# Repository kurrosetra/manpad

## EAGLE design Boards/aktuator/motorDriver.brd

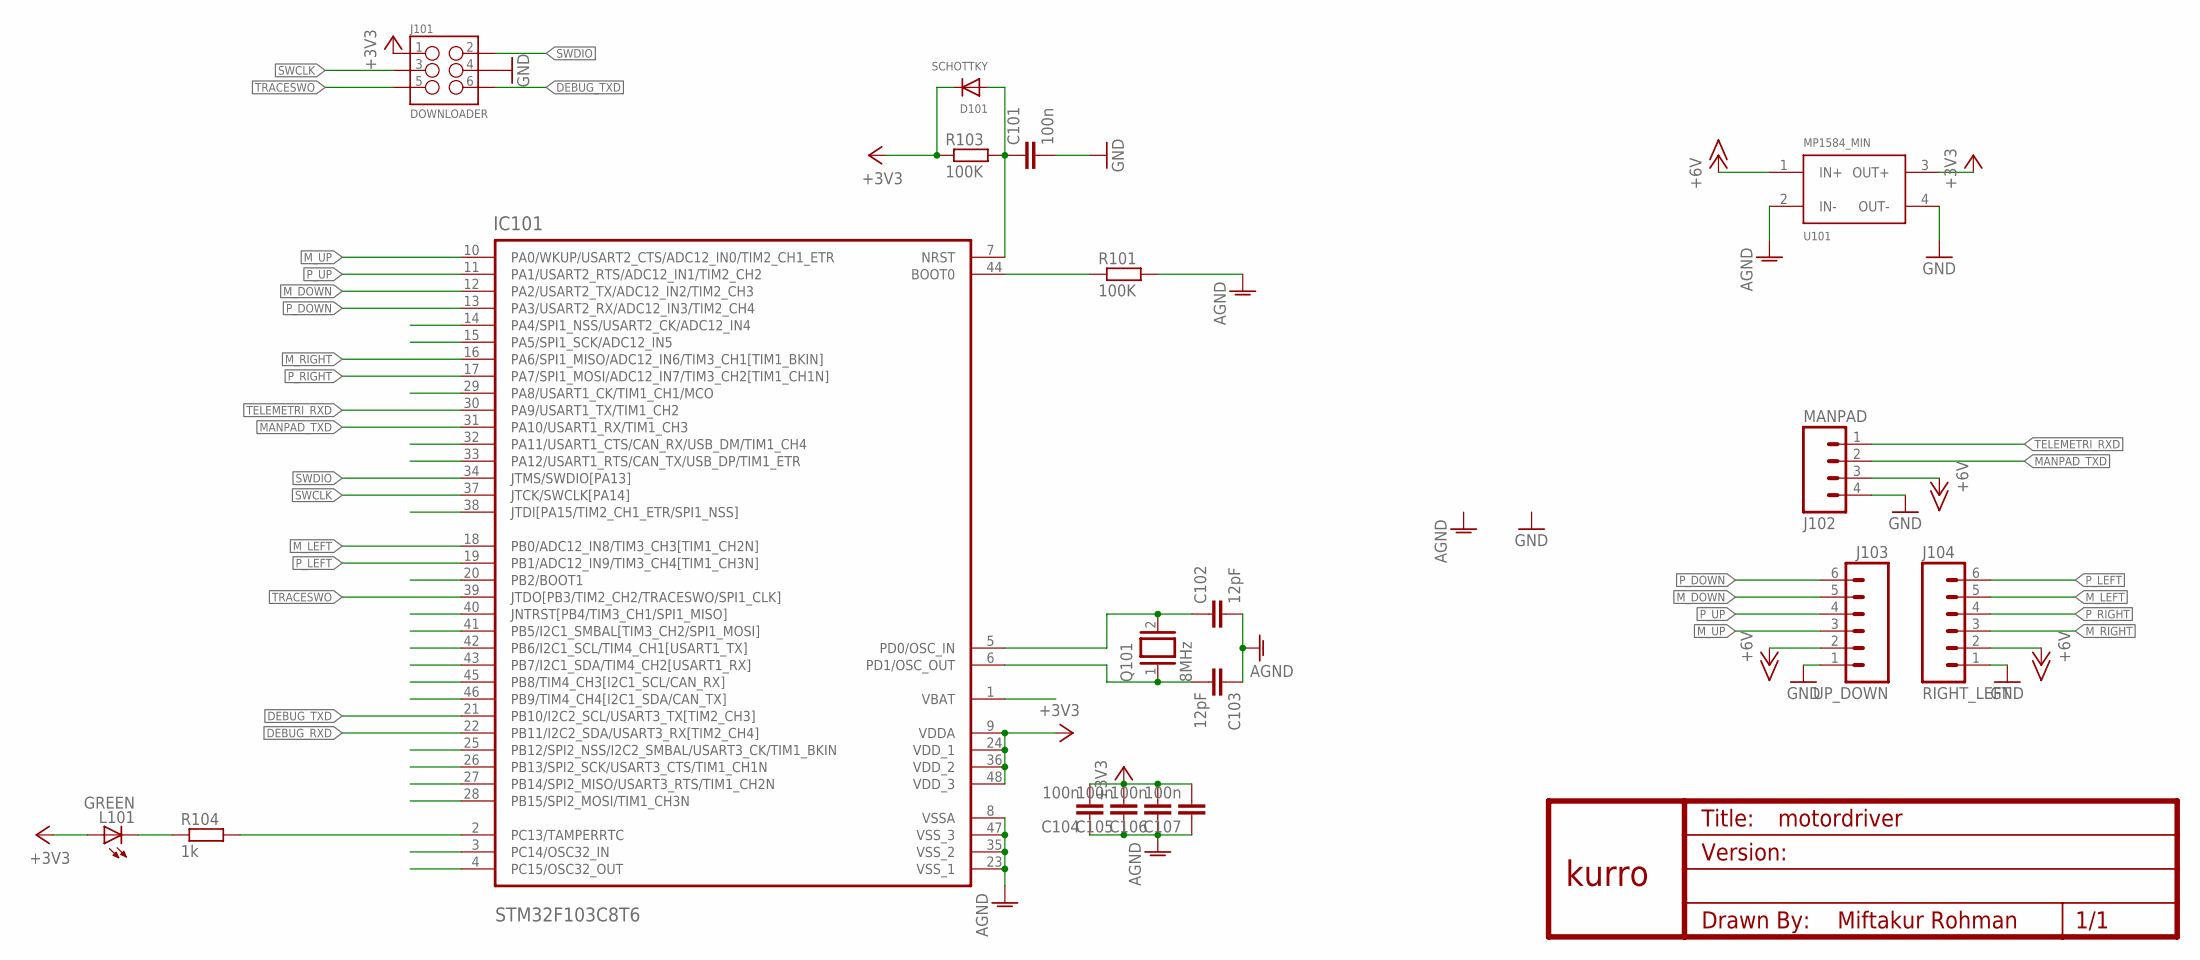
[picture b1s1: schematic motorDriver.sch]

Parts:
C101, C104, C105, C106, C107: 100n; C0603
C102, C103: 12pF; C0603
D101: SCHOTTKY; SOD-323F
IC101: STM32F103C8T6; QFP50P900X900X160-48N
J101: DOWNLOADER; 2X3_SMD
J102: MANPAD; XH-4-VERT-SMD
J103: UP_DOWN; XH-6-VERT-SMD
J104: RIGHT_LEFT; XH-6-VERT-SMD
L101: GREEN; CHIP-LED0805
Q101: 8MHz; QS
R101, R103: 100K; R0603
R104: 1k; R0603
U101: MP1584_MIN
U$1: KURRO_FOOTPRINT; KURRO-LOGO

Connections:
+3V3: C104.2, C105.2, C106.2, C107.2, D101.C, IC101.9 (VDDA), IC101.24 (VDD_1), IC101.36 (VDD_2), IC101.48 (VDD_3), J101.1, L101.A, R103.1, U101.3 (OUT+)
+6V: J102.3, J103.2, J104.2, U101.1 (IN+)
AGND: C102.2, C103.1, C104.1, C105.1, C106.1, C107.1, IC101.8 (VSSA), IC101.23 (VSS_1), IC101.35 (VSS_2), IC101.47 (VSS_3), R101.2, U101.2 (IN-)
DEBUG_RXD: IC101.22 (PB11/I2C2_SDA/USART3_RX[TIM2_CH4])
DEBUG_TXD: IC101.21 (PB10/I2C2_SCL/USART3_TX[TIM2_CH3]), J101.6
GND: C101.2, J101.4, J102.4, J103.1, J104.1, U101.4 (OUT-)
IMU1_SCL: IC101.42 (PB6/I2C1_SCL/TIM4_CH1[USART1_TX])
IMU1_SDA: IC101.43 (PB7/I2C1_SDA/TIM4_CH2[USART1_RX])
LED1_BUILTIN: IC101.2 (PC13/TAMPERRTC), R104.2
MANPAD_TXD: IC101.31 (PA10/USART1_RX/TIM1_CH3), J102.2
M_DOWN: IC101.12 (PA2/USART2_TX/ADC12_IN2/TIM2_CH3), J103.5
M_LEFT: IC101.18 (PB0/ADC12_IN8/TIM3_CH3[TIM1_CH2N]), J104.5
M_RIGHT: IC101.16 (PA6/SPI1_MISO/ADC12_IN6/TIM3_CH1[TIM1_B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), J104.3
M_UP: IC101.10 (PA0/WKUP/USART2_CTS/ADC12_IN0/TIM2_CH1_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), J103.3
unnamed: IC101.44 (BOOT0), R101.1
unnamed: C103.2, IC101.6 (PD1/OSC_OUT), Q101.1
unnamed: C102.1, IC101.5 (PD0/OSC_IN), Q101.2
unnamed: L101.C, R104.1
P_DOWN: IC101.13 (PA3/USART2_RX/ADC12_IN3/TIM2_CH4), J103.6
P_LEFT: IC101.19 (PB1/ADC12_IN9/TIM3_CH4[TIM1_CH3N]), J104.6
P_RIGHT: IC101.17 (PA7/SPI1_MOSI/ADC12_IN7/TIM3_CH2[TIM1_C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), J104.4
P_UP: IC101.11 (PA1/USART2_RTS/ADC12_IN1/TIM2_CH2), J103.4
RST: C101.1, D101.A, IC101.7 (NRST), R103.2
SWCLK: IC101.37 (JTCK/SWCLK[PA14]), J101.3
SWDIO: IC101.34 (JTMS/SWDIO[PA13]), J101.2
TELEMETRI_RXD: IC101.30 (PA9/USART1_TX/TIM1_CH2), J102.1
TRACESWO: IC101.39 (JTDO[PB3/TIM2_CH2/TRACESWO/SPI1_CLK]), J101.5

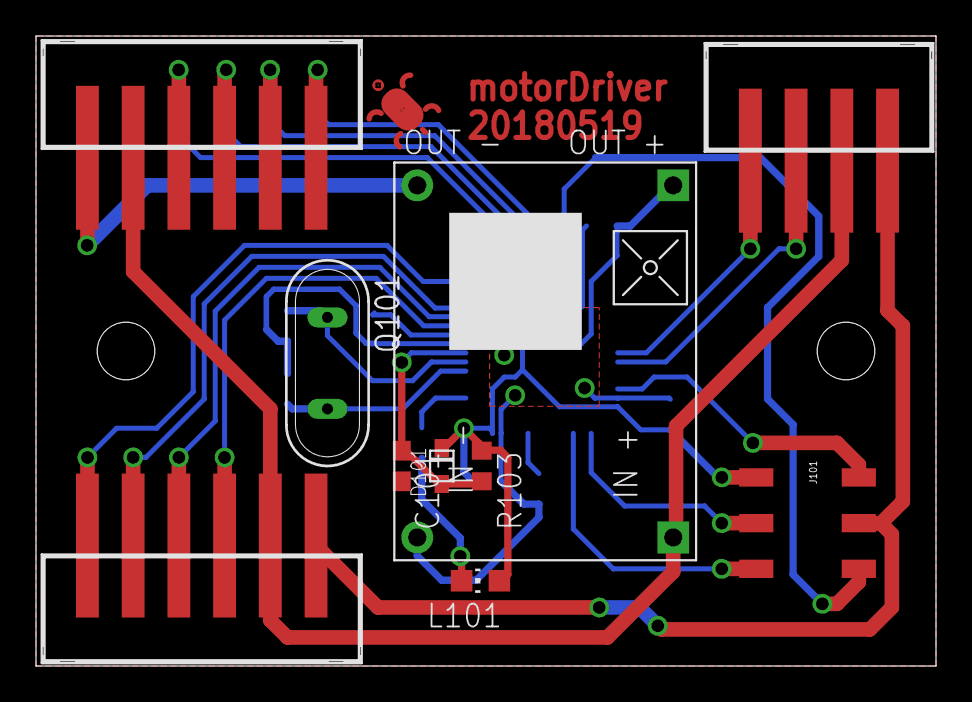
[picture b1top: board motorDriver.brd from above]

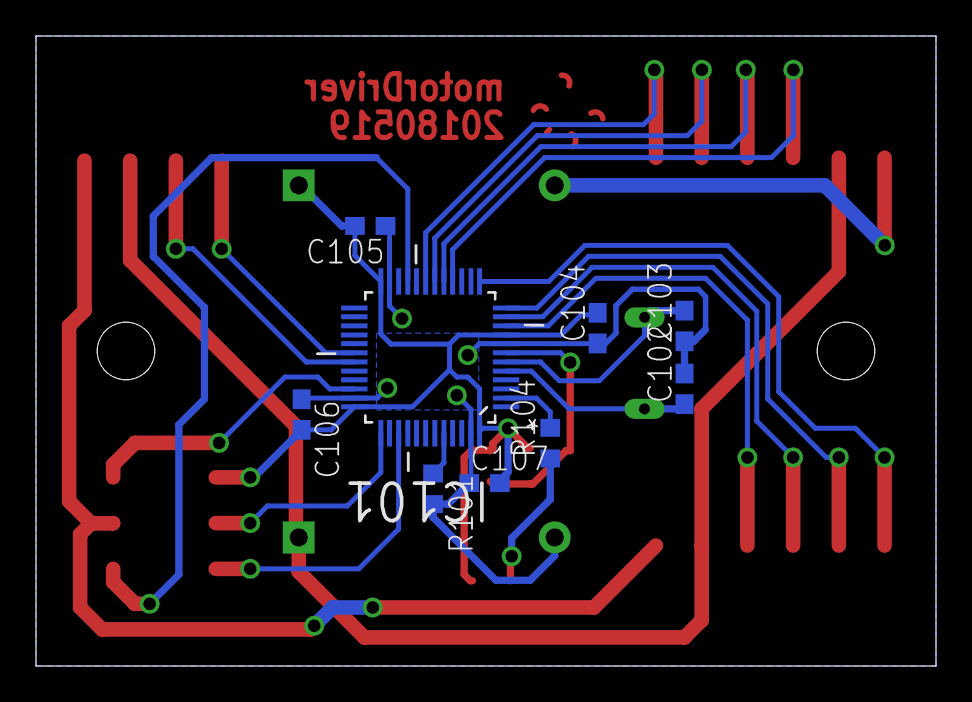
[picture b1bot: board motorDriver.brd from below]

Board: 2 copper layers, 50.0 x 35.0 mm, 20 parts (10 on the bottom side), 24 nets.

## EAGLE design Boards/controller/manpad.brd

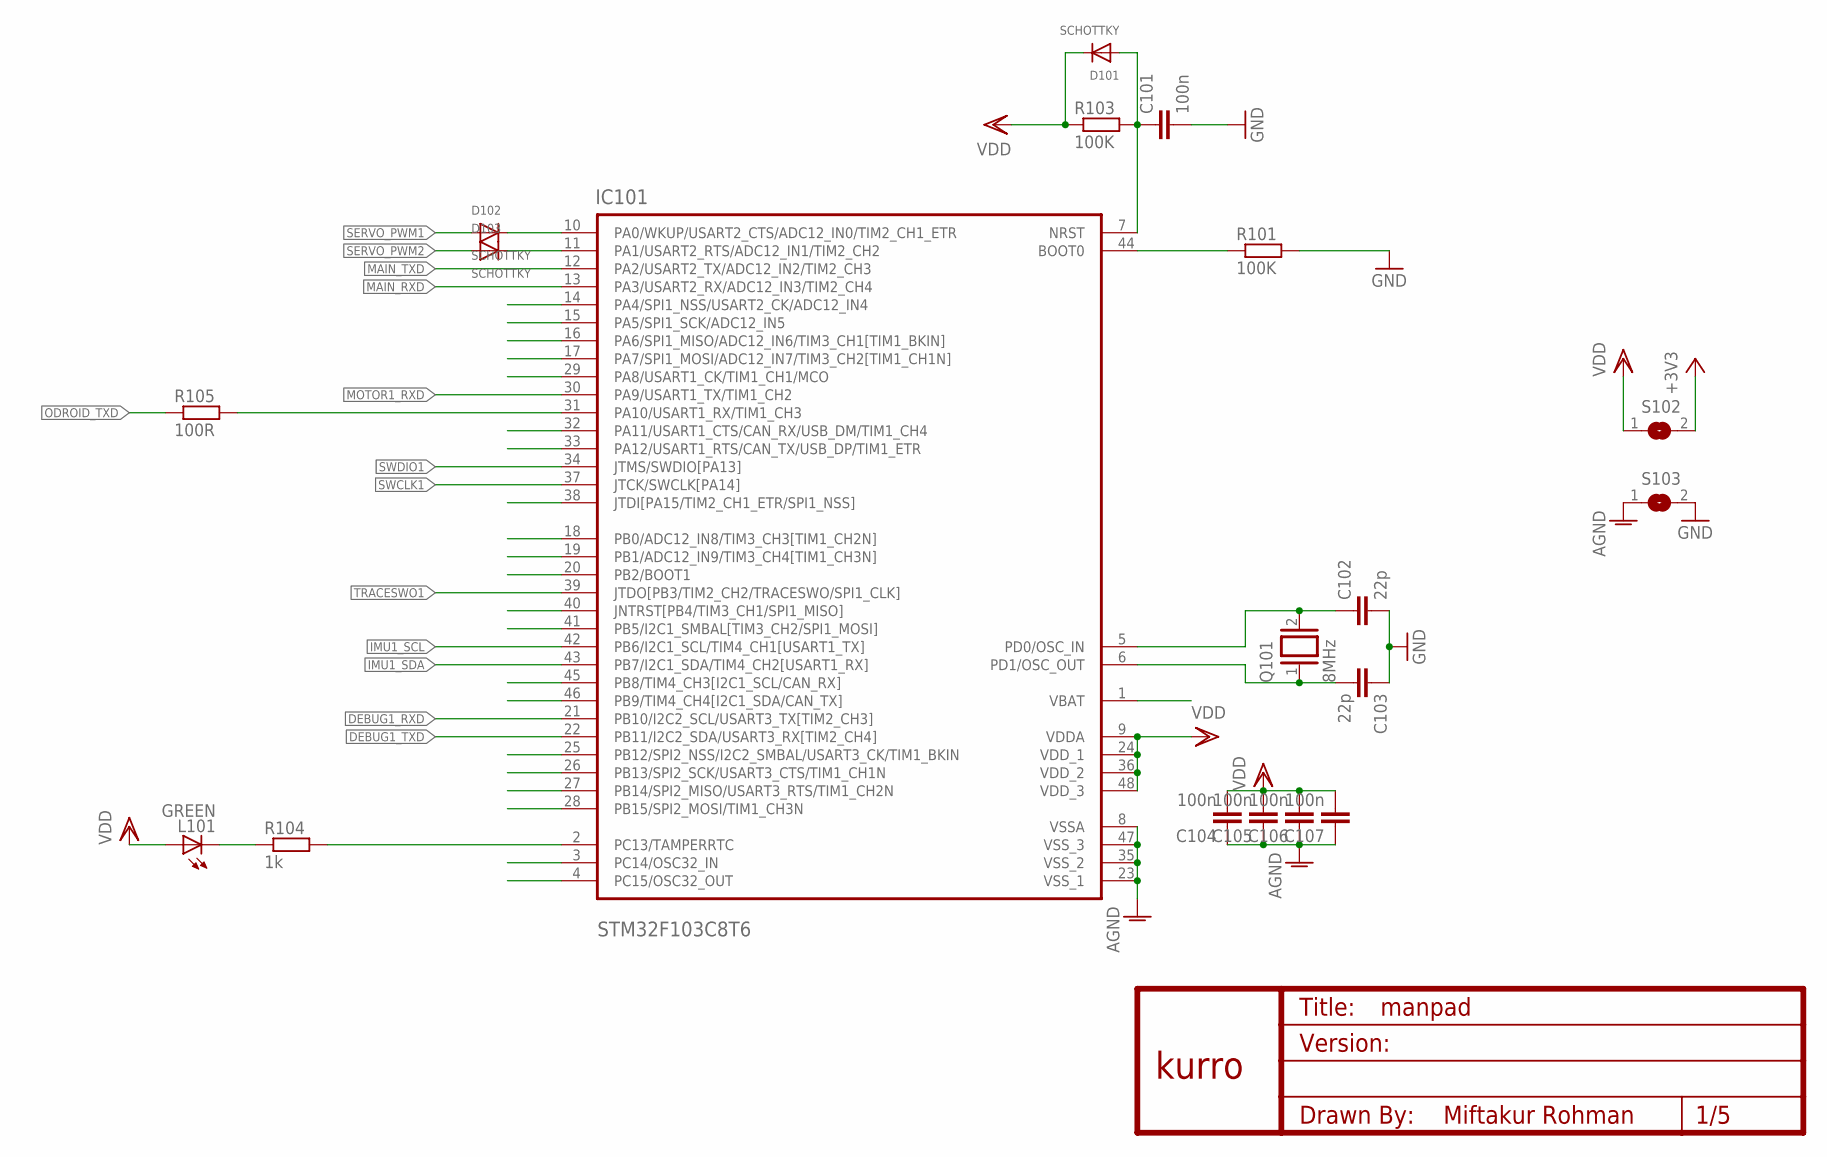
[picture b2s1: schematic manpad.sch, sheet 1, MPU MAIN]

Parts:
C101, C104, C105, C106, C107: 100n; C0603
C102, C103: 22p; C0603
D101, D102, D103: SCHOTTKY; SOD-323F
IC101: STM32F103C8T6; QFP50P900X900X160-48N
L101: GREEN; CHIP-LED0805
Q101: 8MHz; QS
R101, R103: 100K; R0603
R104: 1k; R0603
R105: 100R; R0603
S102, S103: SJS
U$1: KURRO_FOOTPRINT; KURRO-LOGO

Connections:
+3V3: S102.2; also elsewhere on the board
AGND: C104.1, C105.1, C106.1, C107.1, IC101.8 (VSSA), IC101.23 (VSS_1), IC101.35 (VSS_2), IC101.47 (VSS_3), S103.1; also elsewhere on the board
DEBUG1_RXD: IC101.21 (PB10/I2C2_SCL/USART3_TX[TIM2_CH3])
DEBUG1_TXD: IC101.22 (PB11/I2C2_SDA/USART3_RX[TIM2_CH4])
GND: C101.2, C102.2, C103.1, R101.2, S103.2; also elsewhere on the board
IMU1_SCL: IC101.42 (PB6/I2C1_SCL/TIM4_CH1[USART1_TX]); also elsewhere on the board
IMU1_SDA: IC101.43 (PB7/I2C1_SDA/TIM4_CH2[USART1_RX]); also elsewhere on the board
LED1_BUILTIN: IC101.2 (PC13/TAMPERRTC), R104.2
MAIN_RXD: IC101.13 (PA3/USART2_RX/ADC12_IN3/TIM2_CH4); also elsewhere on the board
MAIN_TXD: IC101.12 (PA2/USART2_TX/ADC12_IN2/TIM2_CH3); also elsewhere on the board
MOTOR1_RXD: IC101.30 (PA9/USART1_TX/TIM1_CH2); also elsewhere on the board
unnamed: IC101.44 (BOOT0), R101.1
unnamed: C103.2, IC101.6 (PD1/OSC_OUT), Q101.1
unnamed: C102.1, IC101.5 (PD0/OSC_IN), Q101.2
unnamed: L101.C, R104.1
unnamed: IC101.31 (PA10/USART1_RX/TIM1_CH3), R105.2
ODROID_TXD: R105.1; also elsewhere on the board
PWM1_1: D102.C, IC101.10 (PA0/WKUP/USART2_CTS/ADC12_IN0/TIM2_CH1_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)
PWM2_1: D103.C, IC101.11 (PA1/USART2_RTS/ADC12_IN1/TIM2_CH2)
RST: C101.1, D101.A, IC101.7 (NRST), R103.2
SERVO_PWM1: D102.A; also elsewhere on the board
SERVO_PWM2: D103.A; also elsewhere on the board
SWCLK1: IC101.37 (JTCK/SWCLK[PA14]); also elsewhere on the board
SWDIO1: IC101.34 (JTMS/SWDIO[PA13]); also elsewhere on the board
TRACESWO1: IC101.39 (JTDO[PB3/TIM2_CH2/TRACESWO/SPI1_CLK])
VDD: C104.2, C105.2, C106.2, C107.2, D101.C, IC101.9 (VDDA), IC101.24 (VDD_1), IC101.36 (VDD_2), IC101.48 (VDD_3), L101.A, R103.1, S102.1; also elsewhere on the board

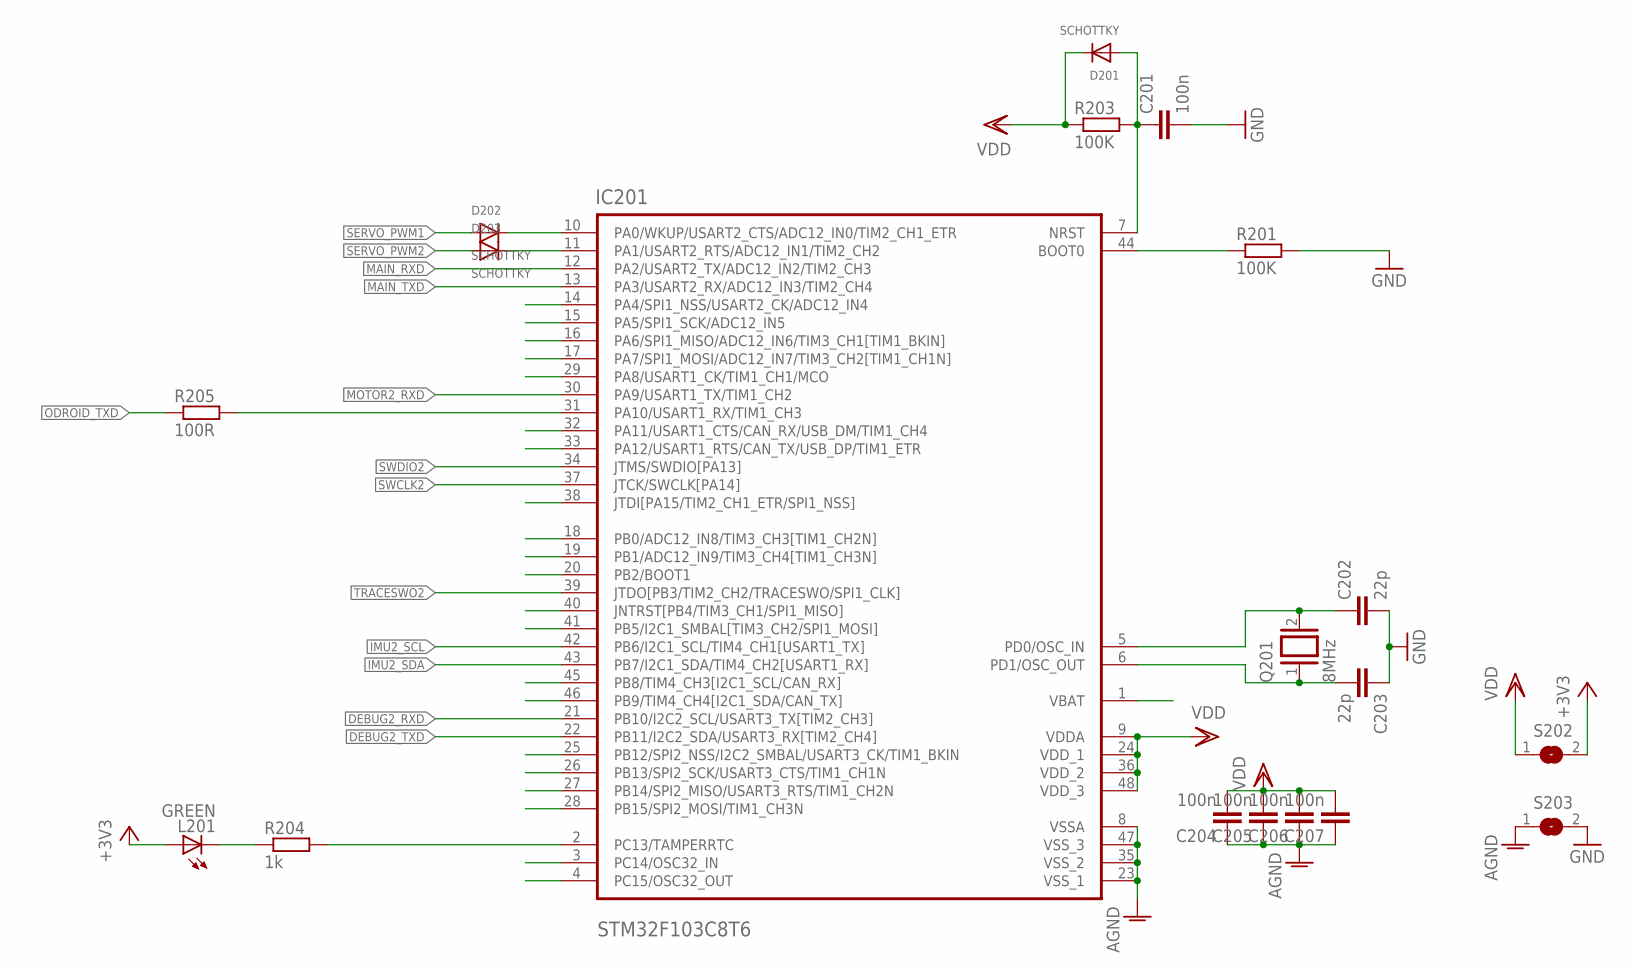
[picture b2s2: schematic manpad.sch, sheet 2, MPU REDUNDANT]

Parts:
C201, C204, C205, C206, C207: 100n; C0603
C202, C203: 22p; C0603
D201, D202, D203: SCHOTTKY; SOD-323F
IC201: STM32F103C8T6; QFP50P900X900X160-48N
L201: GREEN; CHIP-LED0805
Q201: 8MHz; QS
R201, R203: 100K; R0603
R204: 1k; R0603
R205: 100R; R0603
S202, S203: SJS

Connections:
+3V3: L201.A, S202.2; also elsewhere on the board
AGND: C204.1, C205.1, C206.1, C207.1, IC201.8 (VSSA), IC201.23 (VSS_1), IC201.35 (VSS_2), IC201.47 (VSS_3), S203.1; also elsewhere on the board
DEBUG2_RXD: IC201.21 (PB10/I2C2_SCL/USART3_TX[TIM2_CH3])
DEBUG2_TXD: IC201.22 (PB11/I2C2_SDA/USART3_RX[TIM2_CH4])
GND: C201.2, C202.2, C203.1, R201.2, S203.2; also elsewhere on the board
IMU2_SCL: IC201.42 (PB6/I2C1_SCL/TIM4_CH1[USART1_TX]); also elsewhere on the board
IMU2_SDA: IC201.43 (PB7/I2C1_SDA/TIM4_CH2[USART1_RX]); also elsewhere on the board
LED2_BUILTIN: IC201.2 (PC13/TAMPERRTC), R204.2
MAIN_RXD: IC201.12 (PA2/USART2_TX/ADC12_IN2/TIM2_CH3); also elsewhere on the board
MAIN_TXD: IC201.13 (PA3/USART2_RX/ADC12_IN3/TIM2_CH4); also elsewhere on the board
MOTOR2_RXD: IC201.30 (PA9/USART1_TX/TIM1_CH2); also elsewhere on the board
unnamed: IC201.44 (BOOT0), R201.1
unnamed: C203.2, IC201.6 (PD1/OSC_OUT), Q201.1
unnamed: C202.1, IC201.5 (PD0/OSC_IN), Q201.2
unnamed: L201.C, R204.1
unnamed: IC201.31 (PA10/USART1_RX/TIM1_CH3), R205.2
ODROID_TXD: R205.1; also elsewhere on the board
PWM1_2: D202.C, IC201.10 (PA0/WKUP/USART2_CTS/ADC12_IN0/TIM2_CH1_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)
PWM2_2: D203.C, IC201.11 (PA1/USART2_RTS/ADC12_IN1/TIM2_CH2)
RST1: C201.1, D201.A, IC201.7 (NRST), R203.2
SERVO_PWM1: D202.A; also elsewhere on the board
SERVO_PWM2: D203.A; also elsewhere on the board
SWCLK2: IC201.37 (JTCK/SWCLK[PA14]); also elsewhere on the board
SWDIO2: IC201.34 (JTMS/SWDIO[PA13]); also elsewhere on the board
TRACESWO2: IC201.39 (JTDO[PB3/TIM2_CH2/TRACESWO/SPI1_CLK])
VDD: C204.2, C205.2, C206.2, C207.2, D201.C, IC201.9 (VDDA), IC201.24 (VDD_1), IC201.36 (VDD_2), IC201.48 (VDD_3), R203.1, S202.1; also elsewhere on the board

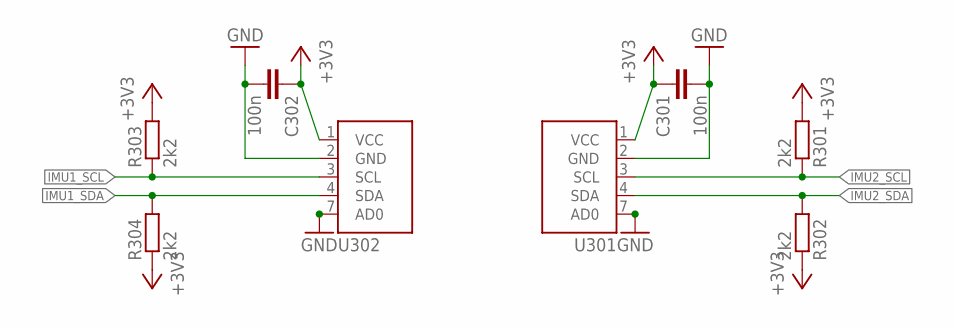
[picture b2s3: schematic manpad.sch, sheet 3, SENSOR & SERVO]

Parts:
C301, C302: 100n; C0603
R301, R302, R303, R304: 2k2; R0603
U301, U302: GY-521_MIN; GY-521_MINNH

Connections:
+3V3: C301.1, C302.1, R301.2, R302.1, R303.2, R304.1, U301.1 (VCC), U302.1 (VCC); also elsewhere on the board
GND: C301.2, C302.2, U301.2 (GND), U301.7 (AD0), U302.2 (GND), U302.7 (AD0); also elsewhere on the board
IMU1_SCL: R303.1, U302.3 (SCL); also elsewhere on the board
IMU1_SDA: R304.2, U302.4 (SDA); also elsewhere on the board
IMU2_SCL: R301.1, U301.3 (SCL); also elsewhere on the board
IMU2_SDA: R302.2, U301.4 (SDA); also elsewhere on the board

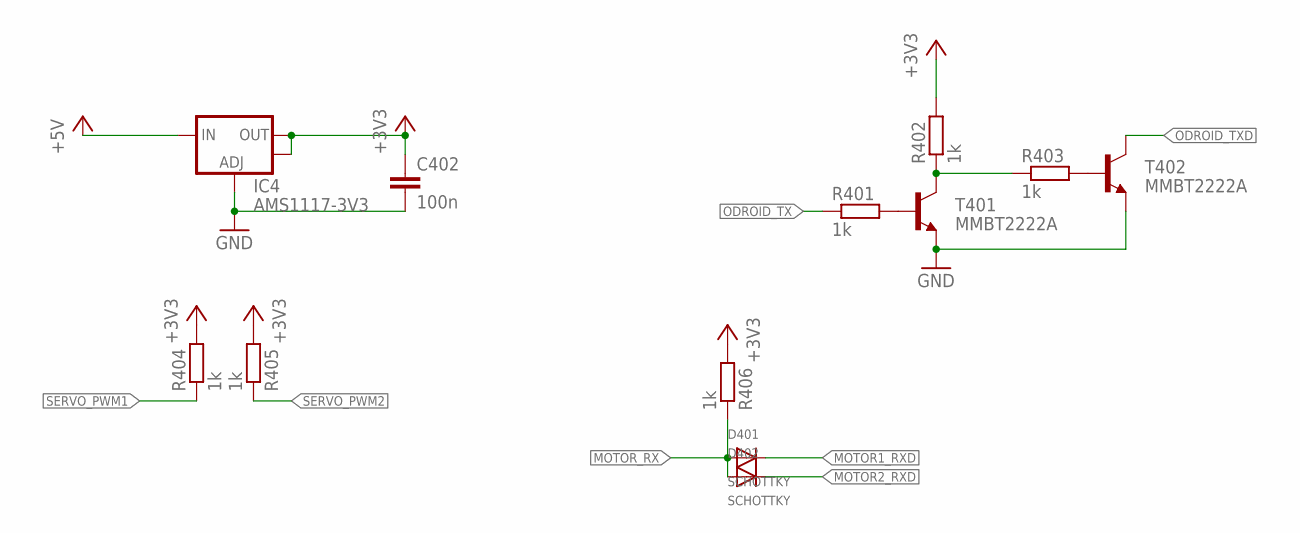
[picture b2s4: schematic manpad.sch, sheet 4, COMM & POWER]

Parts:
C402: 100n; C0603
D401, D402: SCHOTTKY; SOD-323F
IC4: AMS1117-3V3; SOT223
R401, R402, R403, R404, R405, R406: 1k; R0603
T401, T402: MMBT2222A; SOT23

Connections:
+3V3: C402.1, IC4.2 (OUT), IC4.4 (OUT), R402.2, R404.2, R405.2, R406.2; also elsewhere on the board
+5V: IC4.3 (IN); also elsewhere on the board
GND: C402.2, IC4.1 (ADJ), T401.2 (E), T402.2 (E); also elsewhere on the board
MOTOR1_RXD: D401.C; also elsewhere on the board
MOTOR2_RXD: D402.C; also elsewhere on the board
MOTOR_RX: D401.A, D402.A, R406.1; also elsewhere on the board
unnamed: R401.2, T401.1 (B)
unnamed: R402.1, R403.1, T401.3 (C)
unnamed: R403.2, T402.1 (B)
ODROID_TX: R401.1; also elsewhere on the board
ODROID_TXD: T402.3 (C); also elsewhere on the board
SERVO_PWM1: R404.1; also elsewhere on the board
SERVO_PWM2: R405.1; also elsewhere on the board

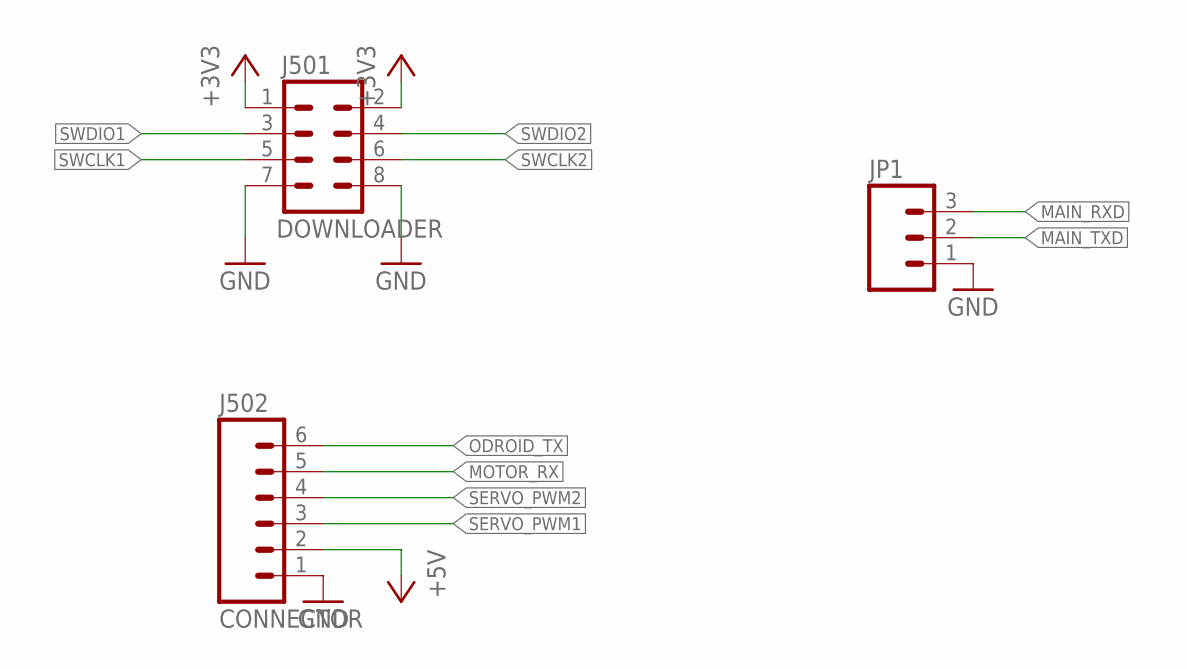
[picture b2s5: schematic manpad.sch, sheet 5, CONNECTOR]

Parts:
J501: DOWNLOADER; 2X4_SMD
J502: CONNECTOR; XH-6-RA
JP1: M03LOCK; 1X03_LOCK

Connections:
+3V3: J501.1, J501.2; also elsewhere on the board
+5V: J502.2; also elsewhere on the board
GND: J501.7, J501.8, J502.1, JP1.1; also elsewhere on the board
MAIN_RXD: JP1.3; also elsewhere on the board
MAIN_TXD: JP1.2; also elsewhere on the board
MOTOR_RX: J502.5; also elsewhere on the board
ODROID_TX: J502.6; also elsewhere on the board
SERVO_PWM1: J502.3; also elsewhere on the board
SERVO_PWM2: J502.4; also elsewhere on the board
SWCLK1: J501.5; also elsewhere on the board
SWCLK2: J501.6; also elsewhere on the board
SWDIO1: J501.3; also elsewhere on the board
SWDIO2: J501.4; also elsewhere on the board

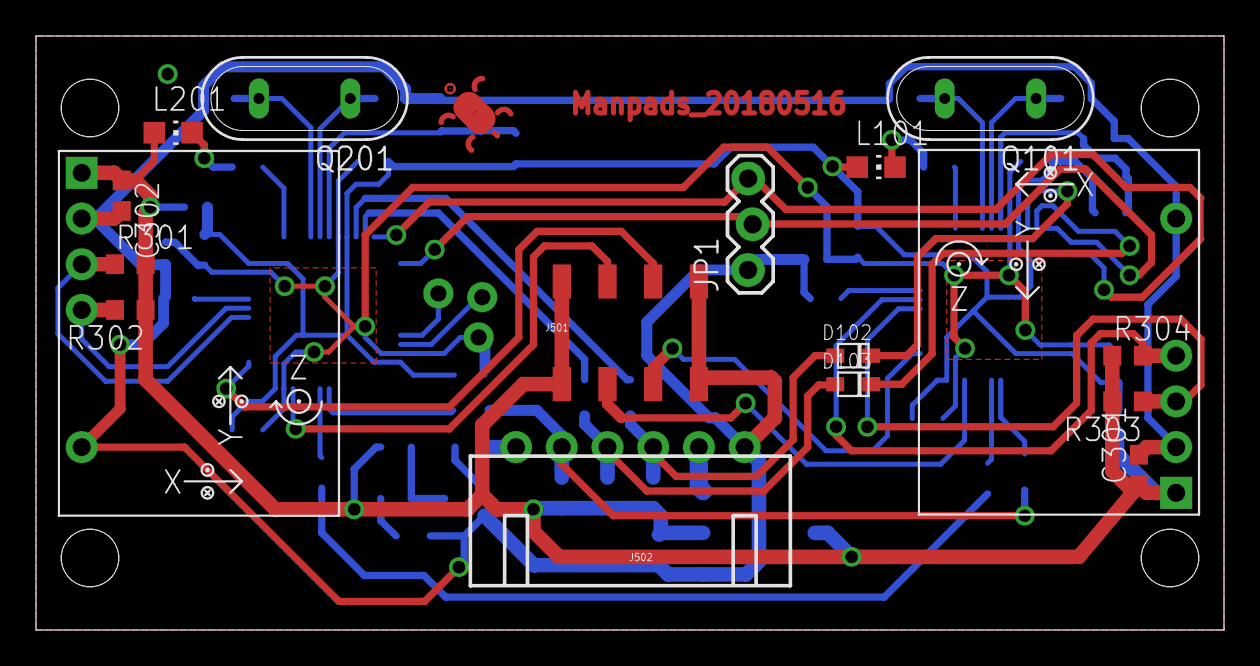
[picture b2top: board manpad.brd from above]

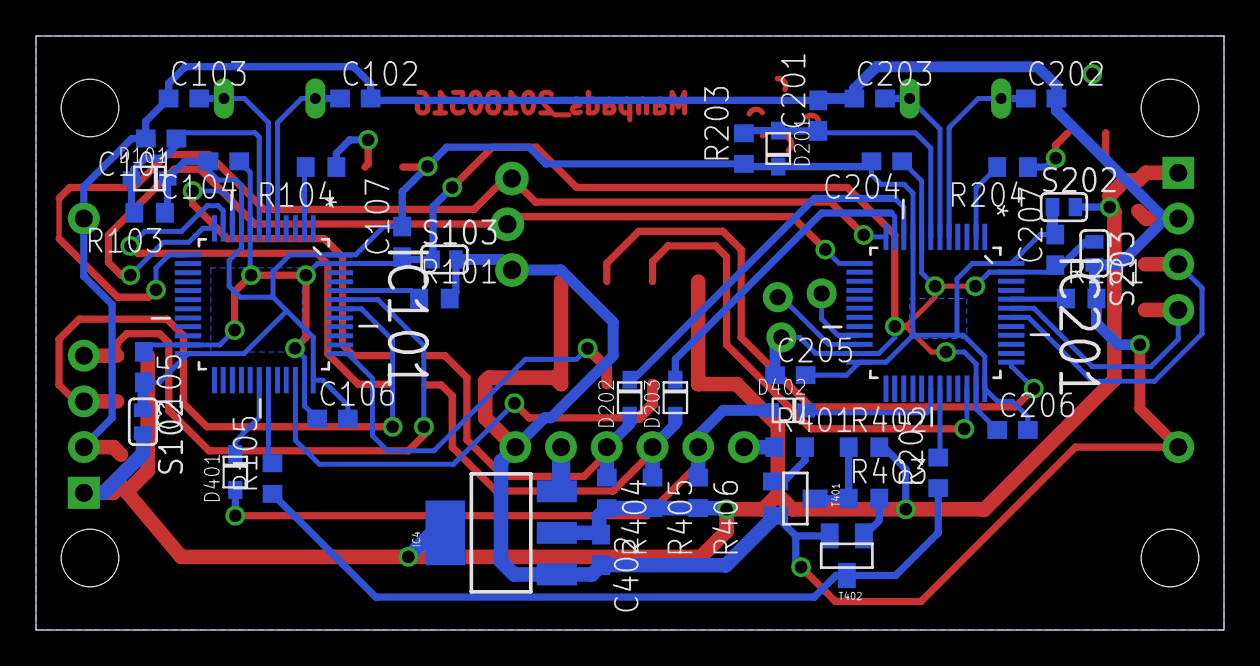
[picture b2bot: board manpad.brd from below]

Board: 2 copper layers, 66.0 x 33.0 mm, 62 parts (45 on the bottom side), 43 nets.

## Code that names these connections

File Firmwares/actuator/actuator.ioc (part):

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Mcu.Name=STM32F103C(8-B)Tx
Mcu.Package=LQFP48
Mcu.UserName=STM32F103C8Tx
PA0-WKUP.GPIOParameters=GPIO_ModeDefaultPP,GPIO_Speed,GPIO_Label
PA0-WKUP.GPIO_Label=M_UP
PA0-WKUP.GPIO_ModeDefaultPP=GPIO_MODE_AF_PP
PA0-WKUP.GPIO_Speed=GPIO_SPEED_FREQ_HIGH
PA0-WKUP.Signal=S_TIM2_CH1_ETR
PA1.GPIOParameters=GPIO_Label
PA1.GPIO_Label=P_UP
PA1.Signal=ADCx_IN1
PA10.GPIOParameters=GPIO_PuPd,GPIO_Label
PA10.GPIO_Label=MANPAD_TXD
PA10.GPIO_PuPd=GPIO_PULLUP
PA10.Mode=Asynchronous
PA10.Signal=USART1_RX
PA13.Mode=Serial_Wire
PA13.Signal=SYS_JTMS-SWDIO
PA14.Mode=Serial_Wire
PA14.Signal=SYS_JTCK-SWCLK
PA2.GPIOParameters=GPIO_ModeDefaultPP,GPIO_Speed,GPIO_Label
PA2.GPIO_Label=M_DOWN
PA2.GPIO_ModeDefaultPP=GPIO_MODE_AF_PP
PA2.GPIO_Speed=GPIO_SPEED_FREQ_HIGH
PA2.Signal=S_TIM2_CH3
PA3.GPIOParameters=GPIO_Label
PA3.GPIO_Label=P_DOWN
PA3.Signal=ADCx_IN3
PA6.GPIOParameters=GPIO_Speed,GPIO_Label
PA6.GPIO_Label=M_RIGHT
PA6.GPIO_Speed=GPIO_SPEED_FREQ_HIGH
PA6.Signal=S_TIM3_CH1
PA7.GPIOParameters=GPIO_Label
PA7.GPIO_Label=P_RIGHT
PA7.Signal=ADCx_IN7
PA9.GPIOParameters=GPIO_Label
PA9.GPIO_Label=TELEMETRI_RXD
PA9.Mode=Asynchronous
PA9.Signal=USART1_TX
PB0.GPIOParameters=GPIO_Speed,GPIO_Label
PB0.GPIO_Label=M_LEFT
PB0.GPIO_Speed=GPIO_SPEED_FREQ_HIGH
PB0.Signal=S_TIM3_CH3
PB1.GPIOParameters=GPIO_Label
PB1.GPIO_Label=P_LEFT
PB1.Signal=ADCx_IN9
PC13-TAMPER-RTC.GPIOParameters=GPIO_Speed,PinState,GPIO_Label
PC13-TAMPER-RTC.GPIO_Label=LED_BUILTIN
PC13-TAMPER-RTC.GPIO_Speed=GPIO_SPEED_FREQ_HIGH
PC13-TAMPER-RTC.PinState=GPIO_PIN_SET
PC13-TAMPER-RTC.Signal=GPIO_Output
PD0-OSC_IN.Mode=HSE-External-Oscillator
PD0-OSC_IN.Signal=RCC_OSC_IN
PD1-OSC_OUT.Mode=HSE-External-Oscillator
PD1-OSC_OUT.Signal=RCC_OSC_OUT
RCC.SYSCLKFreq_VALUE=72000000
RCC.SYSCLKSource=RCC_SYSCLKSOURCE_PLLCLK
board=manpadActuatorDriver

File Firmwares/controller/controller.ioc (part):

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Mcu.Name=STM32F103C(8-B)Tx
Mcu.Package=LQFP48
Mcu.UserName=STM32F103C8Tx
PA0-WKUP.GPIOParameters=GPIO_Speed,GPIO_Label
PA0-WKUP.GPIO_Label=SERVO_ROLL
PA0-WKUP.GPIO_Speed=GPIO_SPEED_FREQ_HIGH
PA0-WKUP.Signal=S_TIM2_CH1_ETR
PA1.GPIOParameters=GPIO_Speed,GPIO_Label
PA1.GPIO_Label=SERVO_PITCH
PA1.GPIO_Speed=GPIO_SPEED_FREQ_HIGH
PA1.Signal=S_TIM2_CH2
PA10.GPIOParameters=GPIO_PuPd
PA10.GPIO_PuPd=GPIO_PULLUP
PA10.Mode=Asynchronous
PA10.Signal=USART1_RX
PA13.Mode=Serial_Wire
PA13.Signal=SYS_JTMS-SWDIO
PA14.Mode=Serial_Wire
PA14.Signal=SYS_JTCK-SWCLK
PA2.Mode=Asynchronous
PA2.Signal=USART2_TX
PA3.Mode=Asynchronous
PA3.Signal=USART2_RX
PA9.Mode=Asynchronous
PA9.Signal=USART1_TX
PB6.Mode=I2C
PB6.Signal=I2C1_SCL
PB7.Mode=I2C
PB7.Signal=I2C1_SDA
PC13-TAMPER-RTC.GPIOParameters=PinState,GPIO_Label
PC13-TAMPER-RTC.GPIO_Label=LED_BUILTIN
PC13-TAMPER-RTC.PinState=GPIO_PIN_SET
PC13-TAMPER-RTC.Signal=GPIO_Output
PD0-OSC_IN.Mode=HSE-External-Oscillator
PD0-OSC_IN.Signal=RCC_OSC_IN
PD1-OSC_OUT.Mode=HSE-External-Oscillator
PD1-OSC_OUT.Signal=RCC_OSC_OUT
RCC.SYSCLKFreq_VALUE=72000000
RCC.SYSCLKSource=RCC_SYSCLKSOURCE_PLLCLK
board=manpadController

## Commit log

2018-09-25 v3.0.0
    MINOR UPDATE:
    1. add boards designs
    2. firmware skeleton for controller
    3. firmware skeleton for actuator
2018-09-26 v3.0.1
    MINOR UPDATE:
    1. controller done, waiting for real test
    2. potential update when acc.z is upside down
    3. potential update when data send to actuator added with log variables
2018-10-04 v3.0.2
    MINOR UPDATE:
    1. uart handler fixed
    2. use ring_buffer for uart RX
2018-10-04 v3.0.2a
    FIX MINOR UPDATE:
    1. limit roll & pitch to lowest value
    2. set LED_BUILTIN speed from "low" to "high"
2018-10-04 v3.0.2b
    FIX MINOR UPDATE:
    1. add inactive command handler (back to zero)
2018-10-05 v3.0.3
    MINOR UPDATE:
    1. fin Right different sign than other
    2. re-initialize rollAngle & pitchAngle when receive servo parameter again (for lab test)
    TODO:
    1. fixing data to be sent as log
    2. for operational mode, add trigger to start fin's movement (acc_x >= ACC_X_TRIGGER)

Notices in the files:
parts and their libraries:
SparkFun: Licensing: CC v3.0 Share-Alike You are welcome to use this library for commercial purposes.
